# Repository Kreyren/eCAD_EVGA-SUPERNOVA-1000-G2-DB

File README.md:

# EVGA SUPERNOVA 1000 G2 Input Power Daughter Board

**REVERSE-ENGINEERED, NOT AN OFFICIAL PRODUCT**

Context: I got this PSU 2nd hand and noticed that it's filled with dust for me to fully disassemble it and clean it to then also notice that the daughter board has it's layer separated in a way that risks connection between the two VAC phases to desolder it and make a new one for me and for people who are in similar situation.

Electronics breakdown: https://www.techpowerup.com/review/evga-supernova-g2-1000/4.html

## SAFETY WARNING

Turning off the power switch **IS NOT ENOUGH TO CUT POWER TO THE RELEVANT COMPONENT**, it only cuts power to one phase, but **THE OTHER PHASE GOES SOMEWHERE IN THE MAINBOARD AND __IS LIVE WITH UP TO 240 VOLTS 10 AMPS ALTERNATE CURRENT, MORE THAN ENOUGH TO KILL YOU OR CAUSE YOU SERIOUS INJURY__!**.

**ALWAYS DISCONNECT FROM POWER AND VERIFY THAT THE POWER SUPPLY IS NOT LIVE WITH APPROPRIATE EQUIPMENT** e.g. CAT III multimeter **__WITH LEADS CERTIFIED ON 240V 10 AMPS ALTERNATE CURRENT__** as the mainboard has a large capacitors **WHICH COULD ELECTROCUTE YOU __EVEN IF THE POWER SUPPLY IS NOT CONNECTED TO POWER__!!**

**ALWAYS PERFORM MAINTANANCE ON THE DEVICE UNDER QUALIFIED SUPERVISION** ideally professional who is certified to provide first aid to electrocuted patients and thus capable of saving your life, as **IN CASE OF AN ELECTROCUTION YOU WILL NEED A DEFIBRILATOR __GENERIC FIRST AID AND HEART MASSAGE IS NOT ENOUGH TO SAVE YOUR LIFE AFTER ELECTROCUTION__** as if current goes through your heart muscles there is a high risk of the current causing the muscles to beat out of sync causing your heart to be unable to oxygenate your blood.

### Additional Notes

EVGA uses film capacitor with wrong rating (305VAC) while the Root Mean Square for 240VAC input power is is 340VAC, thus it's recommended to get an alternative capacitor with sufficient rating.

## How To Fabricate/Order

We are trying to make the design easy to understand and fabricate for everyone interested in the project no matter the age or abilities in designing electrical components, don't hesitate to contact us directly (we will help you for free) or ideally by making a new issue in our repository so that we can adjust the project to make it easier to work with for you and others.

Instrctions for fabrication are provided within the project files and should contain everything you need for fabrication, if something is missing or the fabricator is confused or needs additional details after you provide them the archive with the files then please file an issue in our repository so that we can make the process easier to understand and more intuitive even for those who are not familiar with electrical engineering.

You should always use the files provided in releases for fabrication as using files directly from the repository is likely to cause issues as they go through less strict quality assurance and should always be treated as used only for development.

### Credits

QR Code Generated via https://github.com/lyqht/mini-qr, thanks!

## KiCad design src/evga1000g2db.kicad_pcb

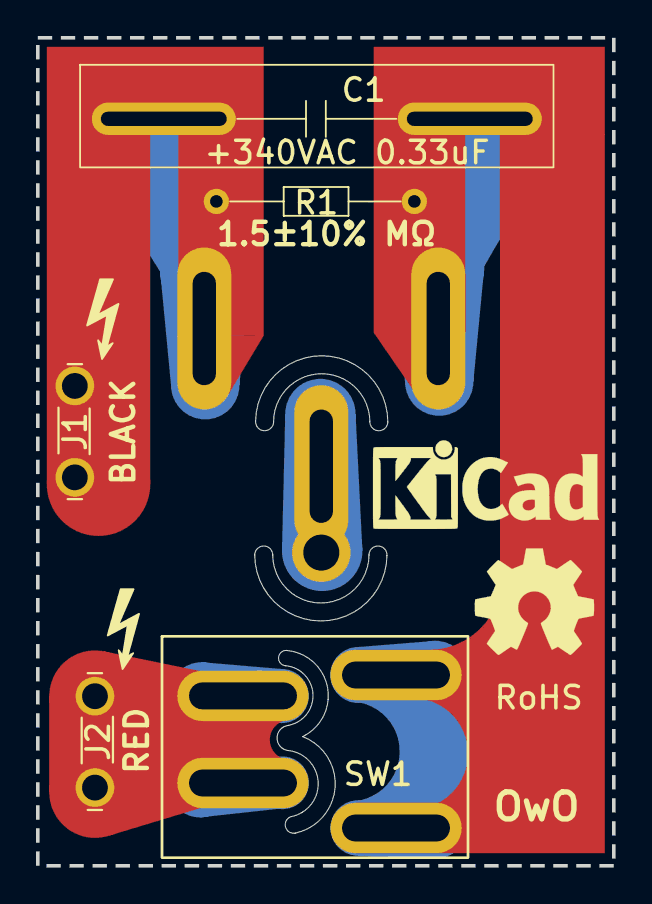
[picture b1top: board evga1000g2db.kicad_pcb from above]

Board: 2 copper layers, 32.0 x 46.0 mm, 6 parts (0 on the bottom side), 3 nets, no tracks yet.

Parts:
C1: 305VAC 0.33 uF K 40/110/56/B (CBB62B); FTK_Capacitor
J1, J2: 62409-1; TE_62409-1
P1: Conn_WallPlug_Earth; IEC_320-C14_Panel_Mount
R1: 1.5±10% MΩ; R_Axial_DIN0204_L3.6mm_D1.6mm_P5.08mm_Horizontal
SW1: SW_DPST; EVGA_Switch

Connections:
unnamed: J2.1, J2.2 (P1), SW1.2
unnamed: C1.1, P1.2 (AC_N), R1.2, SW1.1
unnamed: C1.2, J1.1, J1.2 (P1), P1.1 (AC_P), R1.1

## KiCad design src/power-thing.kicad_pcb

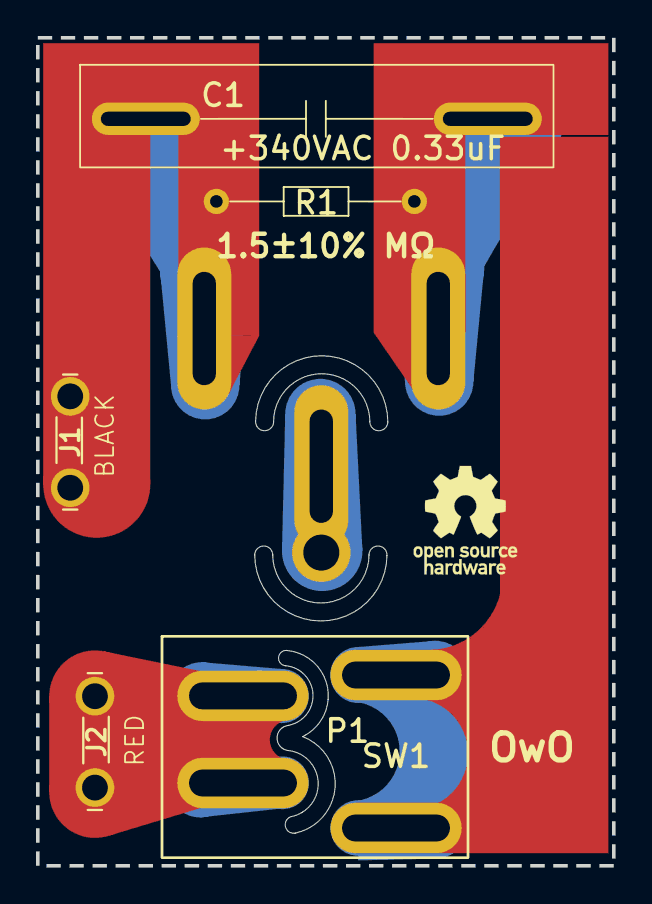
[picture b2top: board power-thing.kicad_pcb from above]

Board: 2 copper layers, 32.0 x 46.0 mm, 6 parts (0 on the bottom side), 3 nets, no tracks yet.

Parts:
C1: 305VAC 0.33 uF K 40/110/56/B (CBB62B); FTK_Capacitor
J1, J2: 62409-1; TE_62409-1
P1: Conn_WallPlug_Earth; IEC_320-C14_Panel_Mount
R1: 1.5±10% MΩ; R_Axial_DIN0204_L3.6mm_D1.6mm_P5.08mm_Horizontal
SW1: SW_DPST; EVGA_Switch

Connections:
unnamed: J2.1, J2.2 (P1), SW1.2
unnamed: C1.1, J1.1, J1.2 (P1), P1.1 (AC_P), R1.1, SW1.1
unnamed: C1.2, P1.2 (AC_N), R1.2

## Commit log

2024-06-26 First implementation
2024-06-26 Adjustments
2024-06-27 sync for bug tracking
2024-06-27 Ready For Review!
2024-06-27 Review Adjustments
2024-06-27 Pre-Release
2024-07-01 better warning
2024-07-02 More adjustments
2024-07-02 sync
2024-07-03 ready to release?
